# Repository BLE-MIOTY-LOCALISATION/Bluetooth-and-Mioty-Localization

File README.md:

This repository contains all the files related to research projects.

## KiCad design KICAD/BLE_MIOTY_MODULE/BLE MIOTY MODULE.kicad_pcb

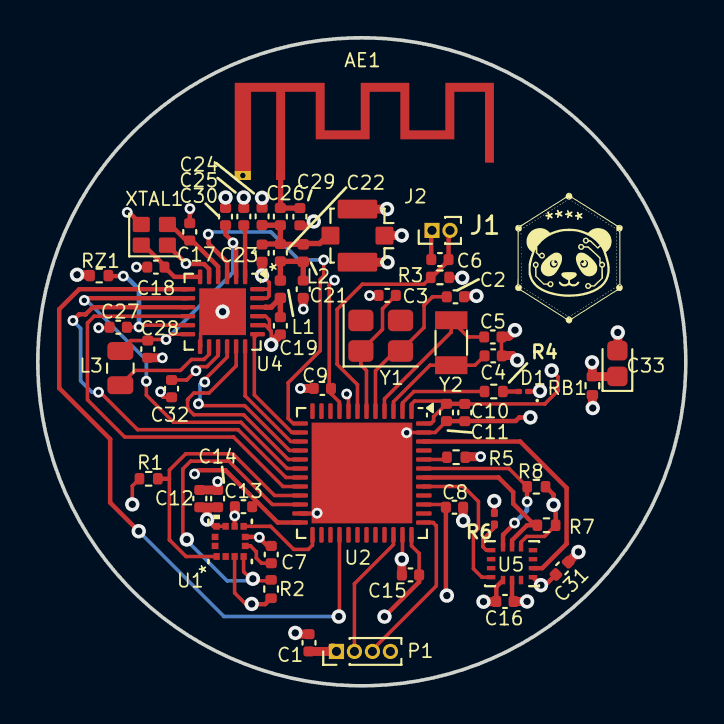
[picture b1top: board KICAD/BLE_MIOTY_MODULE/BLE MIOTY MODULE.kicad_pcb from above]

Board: 4 copper layers, 36.0 x 36.0 mm, 58 parts (1 on the bottom side), 41 nets.

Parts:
AE1: Antenna_Shield; Texas_SWRA117D_2.4GHz_Right
C1, C14: 0.1u; C_0402_1005Metric
C2, C3: 24p; C_0402_1005Metric
C4, C5: 14p; C_0402_1005Metric
C6: 1u; C_0402_1005Metric
C7: 220n; C_0402_1005Metric
C8, C9, C10, C11, C13, C15, C16, C27, C31, C32: 100n; C_0402_1005Metric
C12: 10u; C_0402_1005Metric
C17, C18: 10p; C_0402_1005Metric
C19: 0.8p; C_0402_1005Metric
C21, C23: 1.2p; C_0402_1005Metric
C22: 0.5p; C_0402_1005Metric
C24, C26, C29: 0; C_0402_1005Metric
C25, C30: 10n; C_0402_1005Metric
C28: 470n; C_0402_1005Metric
C33: CP_EIA-1608-08_AVX-J
D1: LED; LED_01005_0402Metric
J1: RST; PinHeader_1x02_P1.00mm_Vertical
J2: Conn_Coaxial; U.FL_Molex_MCRF_73412-0110_Vertical
L1: 3n; L_0402_1005Metric
L2: 2.5n; L_0402_1005Metric
L3: 15u; C_0805_2012Metric
P1: SWD; PinHeader_1x04_P1.00mm_Vertical
R1, R2, R7, R8: 4.7K; R_0402_1005Metric
R3: 10K; R_0402_1005Metric
R4: 2000R; R_0402_1005Metric
R5: 100K; R_0402_1005Metric
R6: 10k; R_0201_0603Metric
RB1: 20; R_0402_1005Metric
RZ1: R; R_0402_1005Metric
U1: IIS2MDCTR; LGA-12_2X2X0P7_STM
U2: STM32F103CBUx; QFN-48-1EP_7x7mm_P0.5mm_EP5.6x5.6mm
U3: CR2032; BatteryHolder_Keystone_3002_1x2032
U4: SX1280IMLTRT; QFN-24-1EP_4x4mm_P0.5mm_EP2.6x2.6mm
U5: ICM-45686; IC_ICM-45686
XTAL1: NX2016SA-52MHZ-EXS00A-CS06016; Crystal_SMD_SeikoEpson_FA128-4Pin_2.0x1.6mm
Y1: 8MHz; Crystal_SMD_3225-4Pin_3.2x2.5mm
Y2: 32.678KHz; Crystal_SMD_3215-2Pin_3.2x1.5mm

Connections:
ANA: C19.2, L1.1, U4.22 (RFIO)
BUSY: U2.28 (PB15), U4.7 (BUSY)
DIO1: U2.18 (PB0), U4.8 (DIO1)
DIO2: U2.19 (PB1), U4.9 (DIO2)
DIO3: U2.20 (PB2), U4.10 (DIO3)
GND: AE1.2 (Shield), C1.1, C2.1, C3.1, C4.1, C5.1, C6.2, C7.2, C8.2, C9.2, C10.2, C11.2, C12.2, C13.2, C14.2, C15.2, C16.2, C17.1, C18.2, C19.1, C21.1, C23.2, C24.2, C25.2, C27.2, C28.2, C29.2, C30.1, C31.2, C32.1, C33.2, D1.1 (K), J1.1, J2.2 (Ext), P1.4, R5.2, R6.2, U1.6 (GND), U1.8 (GND), U2.8 (VSSA), U2.23 (VSS), U2.35 (VSS), U2.47 (VSS), U2.49 (VSS), U3.2, U4.5 (GND), U4.13 (GND), U4.20 (GND), U4.21 (GND), U4.23 (GND), U4.24 (GND), U4.25 (EXP), U5.6 (GND), XTAL1.2, XTAL1.4
INT1A: U2.41 (PB5), U5.4 (INT1/INT)
INT1M: U1.7 (INT/DRDY), U2.25 (PB12)
INT2A: U2.46 (PB9), U5.9 (INT2/FSYNC/CLKIN)
LED: R4.2, U2.2 (PC13)
MISO: U2.16 (PA6), U4.16 (MISO_TX)
MOSI: U2.17 (PA7), U4.17 (MOSI_RX)
NRESET: C6.1, J1.2, R3.2, U2.7 (NRST)
NRST: U2.13 (PA3), U4.3 (~RESET)
NSS: U2.14 (PA4), U4.19 (~SS_CTS)
unnamed: AE1.1 (A), C26.1, C29.1
unnamed: C21.2, C22.2, L1.2, L2.1
unnamed: D1.2 (A), R4.1
unnamed: C22.1, C23.1, C24.1, C26.2, J2.1 (In), L2.2
unnamed: C7.1, U1.5 (C1)
unnamed: R5.1, U2.44 (BOOT0)
unnamed: C28.1, C30.2, L3.2, U4.2 (VDD_IN), U4.12 (DCC_FB)
unnamed: L3.1, U4.14 (DCC_SW)
unnamed: C27.1, RZ1.2, U4.11 (VBAT_IO)
unnamed: C25.1, U4.1 (VR_PA)
unnamed: C17.2, U4.4 (XTA), XTAL1.3
unnamed: C18.1, U4.6 (XTB), XTAL1.1
unnamed: R6.1, U5.1 (AP_SDO/AP_AD0)
OSCIN1: C2.2, U2.5 (PD0), Y1.2
OSCIN2: C4.2, U2.3 (PC14), Y2.2
OSCOUT1: C3.2, U2.6 (PD1), Y1.1
OSCOUT2: C5.2, U2.4 (PC15), Y2.1
SCK: U2.15 (PA5), U4.18 (SCK_~RTS)
SCL 1: R7.2, U2.42 (PB6), U5.13 (AP_SCL/AP_SCLK)
SCL 2: R1.2, U1.1 (SCL/SPC), U2.21 (PB10)
SDA 1: R8.1, U2.43 (PB7), U5.14 (AP_SDA/AP_SDIO/AP_SDI)
SDA 2: R2.2, U1.4 (SDA/SDI/SDO), U2.22 (PB11)
SwDCLK: P1.3, U2.37 (PA14)
SwDIO: P1.2, U2.34 (PA13)
VCC, 3.3V: C1.2, C8.1, C9.1, C10.1, C11.1, C12.1, C13.1, C14.1, C15.1, C16.1, C31.1, C32.2, C33.1, P1.1, R1.1, R2.1, R3.1, R7.1, R8.2, RB1.1, RZ1.1, U1.3 (CS), U1.9 (VDD), U1.10 (VDD_IO), U2.1 (VBAT), U2.9 (VDDA), U2.24 (VDD), U2.36 (VDD), U2.39 (PB3), U2.48 (VDD), U4.15 (VBAT), U5.5 (VDDIO), U5.8 (VDD), U5.12 (AP_CS)
VCC, 3.3V RAW: RB1.2, U3.1

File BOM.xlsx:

S. No. | Schematic No | Component | Details | Part number | URL | Price
Power Supply
1 | RB1 | Resistor | 20 | CRCW040220R0FKED | https://www.digikey.de/de/products/detail/vishay-dale/CRCW04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
2 | U3 | CR2032 | Battery | CR2032 | https://www.digikey.de/de/products/detail/jauch-quartz/CR203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
Reset Mechanism
1 | R3 | Resistor | 10K | CRCW040210K0FKED | https://www.digikey.de/en/products/detail/vishay-dale/CRCW04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
2 | C6 | Capacitor | 1u | C0402C105K8PACTU | https://www.digikey.de/en/products/detail/kemet/C0402C105K8P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
J Link
1 | C1 | Capacitor | 0.1u | CC0402KRX7R9BB104 | https://www.digikey.de/en/products/detail/yageo/CC0402KRX7R9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
Oscillator
1 | Y1 | Crtystal Osc | 8MHx | ECS-80-12-33-JGN-TR | https://www.digikey.de/en/products/detail/ecs-inc/ECS-80-12-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
2 | Y2 | Crtystal Osc | 32KHz | ABS07-32.768KHZ-7-T | https://www.digikey.de/en/products/detail/abracon-llc/abs07-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
3 | C2 | Capacitor | 24p | GRM1555C1H240GA01D | https://www.digikey.de/de/products/detail/murata-electronics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
4 | C3 | Capacitor | 24p | GRM1555C1H240GA01D | https://www.digikey.de/de/products/detail/murata-electronics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
5 | C4 | Capacitor | 14p | GJM1555C1H140GB01D | https://www.digikey.de/de/products/detail/murata-electronics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
6 | C5 | Capacitor | 14p | GJM1555C1H140GB01D | https://www.digikey.de/de/products/detail/murata-electronics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
LED
1 | R4 | Resistor | 2K | CRCW04022K00FKED | https://www.digikey.de/en/products/detail/vishay-dale/CRCW04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
2 | D1 | LED | Blue | XL-1005UBC | https://www.digikey.de/en/products/detail/xinglight/XL-1005U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
Microcontroller
1 | U2 | Microcontroller |  | STM32F103CBU6 | https://www.digikey.de/en/products/detail/stmicroelectronics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
2 | R5 | Resistor | 100K | CRCW0402100KFKED | https://www.digikey.de/en/products/detail/vishay-dale/CRCW04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
3 | C8 | Capacitor | 0.1u | CC0402KRX7R9BB104 | https://www.digikey.de/en/products/detail/yageo/CC0402KRX7R9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
4 | C9 | Capacitor | 0.1u | CC0402KRX7R9BB104 | https://www.digikey.de/en/products/detail/yageo/CC0402KRX7R9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
5 | C10 | Capacitor | 0.1u | CC0402KRX7R9BB104 | https://www.digikey.de/en/products/detail/yageo/CC0402KRX7R9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
6 | C11 | Capacitor | 0.1u | CC0402KRX7R9BB104 | https://www.digikey.de/en/products/detail/yageo/CC0402KRX7R9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
7 | C13 | Capacitor | 0.1u | CC0402KRX7R9BB104 | https://www.digikey.de/en/products/detail/yageo/CC0402KRX7R9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
8 | C15 | Capacitor | 0.1u | CC0402KRX7R9BB104 | https://www.digikey.de/en/products/detail/yageo/CC0402KRX7R9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
LoRa WAN Module
1 | XTAL1 | Crytal oscillator | 52M | CS06016-52M | https://www.digikey.de/de/products/detail/ndk-nihon-dempa-ko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
2 | C17 | Capacitor | 10p | GRM1555C1H100FA01D | https://www.digikey.de/de/products/detail/murata-electronics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
3 | C18 | Capacitor | 10p | GRM1555C1H100FA01D | https://www.digikey.de/de/products/detail/murata-electronics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
4 | L3 | Inductor | 15u | MLZ2012M150W | https://www.digikey.de/en/products/detail/tdk-corporation/ML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
5 | C25 | Capacitor | 10n | GRM155R71E103KA01D | https://www.digikey.de/en/products/detail/murata-electronics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
6 | C27 | Capacitor | 100n | GRM155R71C104KA88D | https://www.digikey.de/en/products/detail/murata-electronics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
7 | RZ1 | Resistor | 0n | CRCW04020000Z0ED | https://www.digikey.de/en/products/detail/vishay-dale/CRCW04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
8 | C32 | Capacitor | 100n | GRM155R71C104KA88D | https://www.digikey.de/en/products/detail/murata-electronics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
9 | C30 | Capacitor | 10n | GRM155R71E103KA01D | https://www.digikey.de/en/products/detail/murata-electronics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
10 | C28 | Capacitor | 470n | GRM155R61A474KE15D | https://www.digikey.de/en/products/detail/murata-electronics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
11 | U4 | Lora Wan |  | SX1280IMLTRT | https://www.digikey.de/en/products/detail/semtech-corporatio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
Antenna Frontend
1 | C19 | capacitor | 0.8p | GRM1555C1HR80BA01D | https://www.digikey.de/en/products/detail/murata-electronics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
2 | L1 | Inductor | 3n | LQW15AN3N0B80D | https://www.digikey.de/en/products/detail/murata-electronics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
3 | C21 | capacitor | 1.2p | GRM1555C1H1R2BA01D | https://www.digikey.de/en/products/detail/murata-electronics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
4 | C22 | capacitor | 0.5p | GRM1555C1HR50WA01D | https://www.digikey.de/en/products/detail/murata-electronics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
5 | L2 | Inductor | 2.5n | LQW15AN2N5C00D | https://www.digikey.de/en/products/detail/murata-electronics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
6 | C23 | capacitor | 1.2p | GRM1555C1H1R2BA01D | https://www.digikey.de/en/products/detail/murata-electronics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
7 | C26 | capacitor | 0
8 | J1 | Connector |  | CONMHF1-SMD-G-T | https://www.digikey.de/de/products/detail/te-connectivity-li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
9 | C24 | capacitor | 0
10 | C29 | capacitor | 0
Tantal Capacitor
1 | C33 | Tantal capacitor | 220u | T491D227K010AT | https://www.digikey.de/en/products/detail/kemet/T491D227K010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
Accelerometer
1 | U5 | Accelerometer | ICM-45686 | ICM-45686 | https://www.digikey.de/de/products/detail/tdk-invensense/ICM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
2 | R6 | Resistor | 10K | CRCW040210K0FKED | https://www.digikey.de/en/products/detail/vishay-dale/CRCW04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
3 | C16 | Capacitor | 0.1u | CC0402KRX7R9BB104 | https://www.digikey.de/en/products/detail/yageo/CC0402KRX7R9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
4 | R7 | Resistor | 4.7K | CRCW04024K70FKED | https://www.digikey.de/de/products/detail/vishay-dale/CRCW04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
5 | R8 | Resistor | 4.7K | CRCW04024K70FKED | https://www.digikey.de/de/products/detail/vishay-dale/CRCW04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
6 | C31 | Capacitor | 0.1u | CC0402KRX7R9BB104 | https://www.digikey.de/en/products/detail/yageo/CC0402KRX7R9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
Magnetometer
1 | U1 | Magnetometer | magnetoresistiv Sensor X, Y, Z Achse 12-LGA (2x2) | IIS2MDCTR | https://www.digikey.de/de/products/detail/stmicroelectronics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
2 | R1 | Resistor | 4.7K | CRCW04024K70FKED | https://www.digikey.de/de/products/detail/vishay-dale/CRCW04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
3 | R2 | Resistor | 4.7K | CRCW04024K70FKED | https://www.digikey.de/de/products/detail/vishay-dale/CRCW04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
4 | C7 | Capacitor | 220n | GRM155R71C224KA12D | https://www.digikey.de/de/products/detail/murata-electronics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
5 | C12 | Capacitor | 10u | GRM155R61A106ME11D | https://www.digikey.de/de/products/detail/murata-electronics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
6 | C14 | Capacitor | 0.1u | CC0402KRX7R9BB104 | https://www.digikey.de/en/products/detail/yageo/CC0402KRX7R9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

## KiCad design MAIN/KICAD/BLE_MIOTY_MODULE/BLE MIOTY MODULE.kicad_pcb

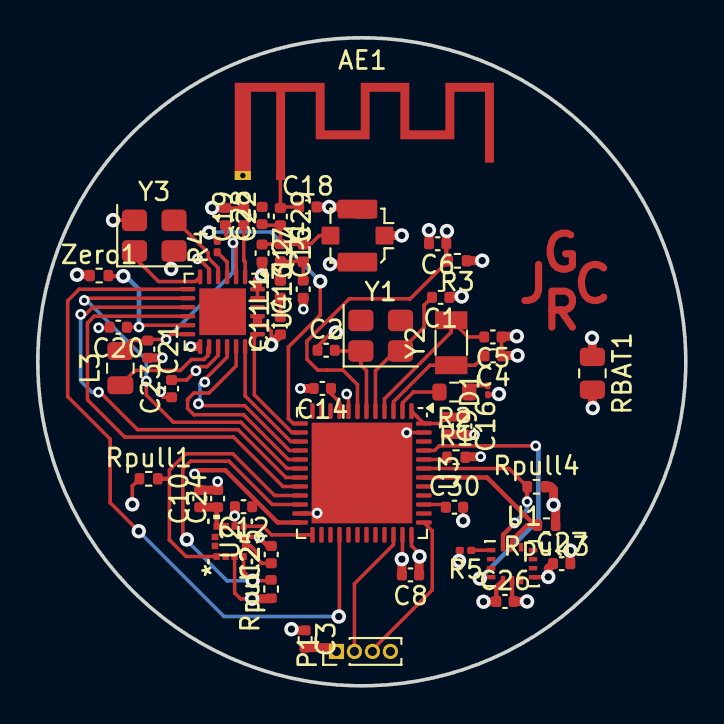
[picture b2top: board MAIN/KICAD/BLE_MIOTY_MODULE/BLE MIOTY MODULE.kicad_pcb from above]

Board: 4 copper layers, 36.0 x 36.0 mm, 55 parts (1 on the bottom side), 42 nets.

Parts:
AE1: Antenna_Shield; Texas_SWRA117D_2.4GHz_Right
C1, C2: 24p; C_0402_1005Metric
C3, C8, C9, C12, C14, C16, C24, C30: 0.1u; C_0402_1005Metric
C4, C5: 14p; C_0402_1005Metric
C6: 1u; C_0402_1005Metric
C10: 10u; C_0402_1005Metric
C11: 0.8p; C_0402_1005Metric
C13, C17: 1.2p; C_0402_1005Metric
C15: 0.5p; C_0402_1005Metric
C18, C28, C29: 0; C_0402_1005Metric
C19, C22: 10n; C_0402_1005Metric
C20, C23: 100n; C_0402_1005Metric
C21: 470n; C_0402_1005Metric
C25, C26, C27: 220n; C_0402_1005Metric
D1: LED; LED_01005_0402Metric
J1: Conn_Coaxial; U.FL_Molex_MCRF_73412-0110_Vertical
L1: 3n; L_0402_1005Metric
L2: 2.5n; L_0402_1005Metric
L3: 15u; C_0805_2012Metric
P1: SWD; PinHeader_1x04_P1.00mm_Vertical
R1: 100K; R_0402_1005Metric
R2: 2000R; R_0603_1608Metric
R3: 10K; R_0402_1005Metric
R4: R; R_0201_0603Metric
R5: 10k; R_0201_0603Metric
RBAT1: 20; R_0805_2012Metric
Rpull1, Rpull2, Rpull3, Rpull4: 4.7K; R_0402_1005Metric
U1: ICM-45686; IC_ICM-45686
U2: IIS2MDCTR; LGA-12_2X2X0P7_STM
U3: STM32F103CBUx; QFN-48-1EP_7x7mm_P0.5mm_EP5.6x5.6mm
U4: SX1280IMLTRT; QFN-24-1EP_4x4mm_P0.5mm_EP2.6x2.6mm
U5: CR2032; BatteryHolder_Keystone_3002_1x2032
Y1: 8MHz; Crystal_SMD_3225-4Pin_3.2x2.5mm
Y2: 32.678KHz; Crystal_SMD_3215-2Pin_3.2x1.5mm
Y3: 52M; Crystal_SMD_3225-4Pin_3.2x2.5mm
Zero1: R; R_0402_1005Metric

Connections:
ANA: C11.2, L1.1, U4.22 (RFIO)
BUSY: U3.28 (PB15), U4.7 (BUSY)
DIO1: U3.18 (PB0), U4.8 (DIO1)
DIO2: U3.19 (PB1), U4.9 (DIO2)
DIO3: U3.20 (PB2), U4.10 (DIO3)
GND: AE1.2 (Shield), C1.1, C2.1, C3.1, C4.1, C5.1, C6.2, C8.2, C9.2, C10.2, C11.1, C12.2, C13.1, C14.2, C16.2, C17.2, C18.2, C19.2, C20.2, C21.2, C22.1, C23.1, C24.2, C25.2, C26.2, C27.2, C28.2, C30.2, D1.1 (K), J1.2 (Ext), P1.4, R1.2, R5.2, U1.6 (GND), U2.6 (GND), U2.8 (GND), U3.8 (VSSA), U3.23 (VSS), U3.35 (VSS), U3.47 (VSS), U3.49 (VSS), U4.5 (GND), U4.13 (GND), U4.20 (GND), U4.21 (GND), U4.23 (GND), U4.24 (GND), U5.2, Y3.2, Y3.4
INT1: U1.4 (INT1/INT), U3.45 (PB8)
INT2: U2.7 (INT/DRDY), U3.25 (PB12)
LED: R2.2, U3.2 (PC13)
MISO: U3.16 (PA6), U4.16 (MISO_TX)
MOSI: U3.17 (PA7), U4.17 (MOSI_RX)
NRESET: C6.1, R3.2, U3.7 (NRST)
NRST: R4.2, U3.13 (PA3)
NSS: U3.14 (PA4), U4.19 (~SS_CTS)
unnamed: AE1.1 (A), C18.1, C29.1
unnamed: C13.2, C15.2, L1.2, L2.1
unnamed: D1.2 (A), R2.1
unnamed: C15.1, C17.1, C28.1, C29.2, J1.1 (In), L2.2
unnamed: R5.1, U1.1 (AP_SDO/AP_AD0)
unnamed: C25.1, U2.5 (C1)
unnamed: C10.1, C24.1, U2.9 (VDD), U2.10 (VDD_IO)
unnamed: R1.1, U3.44 (BOOT0)
unnamed: C21.1, C22.2, L3.2, U4.2 (VDD_IN), U4.12 (DCC_FB)
unnamed: L3.1, U4.14 (DCC_SW)
unnamed: C20.1, U4.11 (VBAT_IO), Zero1.2
unnamed: C19.1, U4.1 (VR_PA)
unnamed: U4.4 (XTA), Y3.3
unnamed: U4.6 (XTB), Y3.1
unnamed: R4.1, U4.3 (~RESET)
OSCIN1: C1.2, U3.5 (PD0), Y1.2
OSCIN2: C4.2, U3.3 (PC14), Y2.2
OSCOUT1: C2.2, U3.6 (PD1), Y1.1
OSCOUT2: C5.2, U3.4 (PC15), Y2.1
SCK: U3.15 (PA5), U4.18 (SCK_~RTS)
SCL 1: Rpull3.2, U1.13 (AP_SCL/AP_SCLK), U3.42 (PB6)
SCL 2: Rpull1.2, U2.1 (SCL/SPC), U3.21 (PB10)
SDA 1: Rpull4.1, U1.14 (AP_SDA/AP_SDIO/AP_SDI), U3.43 (PB7)
SDA 2: Rpull2.2, U2.4 (SDA/SDI/SDO), U3.22 (PB11)
SwDCLK: P1.3, U3.37 (PA14)
SwDIO: P1.2, U3.34 (PA13)
VCC, 3.3V: C3.2, C8.1, C9.1, C12.1, C14.1, C16.1, C23.2, C26.1, C27.1, C30.1, P1.1, R3.1, RBAT1.1, Rpull1.1, Rpull2.1, Rpull3.1, Rpull4.2, U1.5 (VDDIO), U1.8 (VDD), U2.3 (CS), U3.1 (VBAT), U3.9 (VDDA), U3.24 (VDD), U3.36 (VDD), U3.39 (PB3), U3.48 (VDD), U4.15 (VBAT), Zero1.1
VCC, 3.3V RAW: RBAT1.2, U5.1

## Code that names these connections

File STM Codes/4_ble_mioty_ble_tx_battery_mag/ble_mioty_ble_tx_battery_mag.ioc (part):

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Mcu.Name=STM32F103CBUx
Mcu.Package=UFQFPN48
Mcu.UserName=STM32F103CBUx
PA13.Mode=Serial_Wire
PA13.Signal=SYS_JTMS-SWDIO
PA14.Mode=Serial_Wire
PA14.Signal=SYS_JTCK-SWCLK
PA4.GPIOParameters=GPIO_Label
PA4.GPIO_Label=LORA_NSS
PA4.Signal=GPIO_Output
PA5.Mode=Full_Duplex_Master
PA5.Signal=SPI1_SCK
PA6.Mode=Full_Duplex_Master
PA6.Signal=SPI1_MISO
PA7.Mode=Full_Duplex_Master
PA7.Signal=SPI1_MOSI
PB0.GPIOParameters=GPIO_Label
PB0.GPIO_Label=LORA_DIO1
PB0.Signal=GPIO_Input
PB10.Mode=I2C
PB10.Signal=I2C2_SCL
PB11.Mode=I2C
PB11.Signal=I2C2_SDA
PB12.GPIOParameters=GPIO_Label
PB12.GPIO_Label=MAG INT
PB12.Signal=GPXTI12
PB15.GPIOParameters=GPIO_Label
PB15.GPIO_Label=LORA_BUSY
PB15.Signal=GPIO_Input
PC13-TAMPER-RTC.GPIOParameters=GPIO_Label
PC13-TAMPER-RTC.GPIO_Label=LED
PC13-TAMPER-RTC.Signal=GPIO_Output
PC14-OSC32_IN.Mode=LSE-External-Oscillator
PC14-OSC32_IN.Signal=RCC_OSC32_IN
PC15-OSC32_OUT.Mode=LSE-External-Oscillator
PC15-OSC32_OUT.Signal=RCC_OSC32_OUT
PD0-OSC_IN.Mode=HSE-External-Oscillator
PD0-OSC_IN.Signal=RCC_OSC_IN
PD1-OSC_OUT.Mode=HSE-External-Oscillator
PD1-OSC_OUT.Signal=RCC_OSC_OUT
RCC.SYSCLKFreq_VALUE=8000000
RCC.SYSCLKSource=RCC_SYSCLKSOURCE_HSE
board=custom

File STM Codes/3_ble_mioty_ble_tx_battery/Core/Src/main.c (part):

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  uint8_t crc_seed[3] = {0x55, 0x55, 0x55};
  SX1280_WriteRegister(0x09C7, crc_seed, 3);

  // 8. Map TxDone IRQ to DIO1 pin
  //    [opcode, IRQmask_H, IRQmask_L, DIO1_H, DIO1_L, DIO2_H, DIO2_L, DIO3_H,
  //    DIO3_L]
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// -----------------------------------------------------------------------
// Transmit one BLE ADV_NONCONN_IND packet on the specified channel
//
// Returns: 1 = TxDone confirmed via DIO1 pin
//          0 = TxDone not seen (possible TX failure)
//
// DIO1 is mapped to TxDone IRQ in InitBLE step 8.
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  SX1280_WaitBusy();
  HAL_Delay(2);

  // Read TxDone confirmation from DIO1 pin
  uint8_t txdone = 0;
  if (HAL_GPIO_ReadPin(LORA_DIO1_GPIO_Port, LORA_DIO1_Pin) == GPIO_PIN_SET) {
    txdone = 1;
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  __HAL_SPI_DISABLE(&hspi1);

  GPIO_InitTypeDef GPIO_InitStruct = {0};
  // SCK (PA5), MISO (PA6), MOSI (PA7) -> Input with Pull-Down (prevents floating SPI bus)
  GPIO_InitStruct.Pin = GPIO_PIN_5 | GPIO_PIN_6 | GPIO_PIN_7;
  GPIO_InitStruct.Mode = GPIO_MODE_INPUT;
  GPIO_InitStruct.Pull = GPIO_PULLDOWN;
  HAL_GPIO_Init(GPIOA, &GPIO_InitStruct);

  // DIO1 (PB0) and BUSY (PB15) -> Input with Pull-Down
  GPIO_InitStruct.Pin = LORA_DIO1_Pin | LORA_BUSY_Pin;
  GPIO_InitStruct.Mode = GPIO_MODE_INPUT;
  GPIO_InitStruct.Pull = GPIO_PULLDOWN;
  HAL_GPIO_Init(GPIOB, &GPIO_InitStruct);

  // Keep NSS (PA4) and NRST (PA3) HIGH to lock radio state
  HAL_GPIO_WritePin(LORA_NSS_GPIO_Port, LORA_NSS_Pin, GPIO_PIN_SET);
  HAL_GPIO_WritePin(LORA_NRST_GPIO_Port, LORA_NRST_Pin, GPIO_PIN_SET);

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  HAL_SPI_DeInit(&hspi1);
  MX_SPI1_Init();

  // 9. Re-initialize DIO1 (PB0) and BUSY (PB15) as INPUT, NOPULL
  GPIO_InitStruct.Pin = LORA_DIO1_Pin | LORA_BUSY_Pin;
  GPIO_InitStruct.Mode = GPIO_MODE_INPUT;
  GPIO_InitStruct.Pull = GPIO_NOPULL;
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
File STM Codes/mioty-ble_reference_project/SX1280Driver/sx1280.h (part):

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#include <cmath>

/*!
 * \brief GPIO pin number connected to DIO1 on the SX1280 radio module.
 *
 * DIO1 is used by the SX1280 to signal events like payload ready, transmission done, etc.
 * This pin must be configured as an input and, depending on the specific use case,
 * may need to trigger interrupts.
 */
#define PIN_DIO1 2

/*!
 * \brief GPIO pin number connected to DIO2 on the SX1280 radio module.
 *
 * DIO2 is typically used for signaling events such as FHSS frequency change, CAD detection, etc.
 * Similar to DIO1, this pin should be configured based on the intended radio functionalities being used.
 */
#define PIN_DIO2 3

/*!
 * \brief GPIO pin number connected to DIO3 on the SX1280 radio module.
 *
 * DIO3 can be used for additional event signaling from the SX1280, which may include timing or synchronization signals.
 * Configuration and use will depend on the SX1280's operational mode and setup.
 */
#define PIN_DIO3 4

/*!
 * \brief Provides the frequency of the chip running on the radio and the frequency step
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
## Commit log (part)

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2025-07-01 Previous Project Injection
2025-07-01 Progress 1
2025-08-13 Added a new folder and datsheets
2025-08-15 updated kicad design and bluepill schematic files
2025-08-15 Added CR2032, start with PCB schematic
2025-08-15 Did something
2025-08-18 Updated Repo Structure, updated schematic v1.1
2025-08-20 Updated PCB Design
2025-09-03 latest with lad9s1 acc and tantal
2025-09-03 Updated latest with all files
2025-09-11 Updated components acording to BOM
2025-10-14 New Beginings
2025-10-14 Organization
2025-10-14 Some more
2025-10-16 updated Link in BOM
2025-10-16 Deleting V2
2025-10-16 Added 5 Caps, Excel changes
2025-10-16 Y3 Tental Pending, Start PCB, BOM Updated
2025-10-17 latest push
2025-10-17 PCB Premier League
2025-10-17 RCBavaria First Push
2025-10-23 Fresh PCB start
2025-10-23 RC: Added Footprints Folder, Added New IMUs Sym/ Footprint
2025-10-23 Sync
2025-10-23 STM ref
2025-10-23 first proto
2025-10-27 new design on main
2025-10-27 minor change
2025-10-31 sync 2
2025-10-31 Sync 3
2025-11-05 final push
    updated BOM and PCB
2025-12-03 Latest changes with 0 errors effective
2025-12-03 change of track width required
2025-12-04 Final Design for Production
2025-12-11 sync with BOM
2026-05-21 blink code with blue pill working
2026-05-21 pin update
2026-05-27 Clean Up
2026-05-29 Folder Management
2026-06-05 LORA Bring Up Done
2026-06-05 Lora TX code, updated Schematic (fix duplicate annotations), exported netlist
2026-06-05 Added BLE TX STM Code
2026-06-07 9-6-3 latest
2026-06-10 Transmitter Woring, BLE N/A
2026-06-10 Few Changes
2026-06-11 BLE Working
2026-06-11 Updated Schematic, BOM, Add Symbols and completed 3d view
2026-06-11 Update BOM, remove lock file
2026-06-11 changed tantal ref C33
2026-06-11 Updated PCB, Schematic, 3D Model
2026-06-11 removed lc files
2026-06-24 Remove old PlatformIO files and add GoogleFindMyTools and MIOTY_BLE_Tests which includes optimized Ble_tx_codes
2026-06-25 feat(power-opt): fix compilation, enable LSE/Low-power loop, and correct LED polarity
    - Fix compilation by declaring volatile 'alarm_fired' flag.
    - Populate empty main loop with BLE beacon transmission and Stop Mode entry.
    - Configure LORA_NRST (PA3) as GPIO output to prevent floating radio reset states.
    - Correct LED pin mapping for active-high polarity to eliminate sleep current leakage.
    - Switch RTC clock source to LSE (32.768 kHz) with a 32767 prescaler for accurate 1 Hz wakeup.
    - Add RSF flag synchronization to RTC_SetAlarm_1s() to prevent corrupted register reads after Stop Mode wakeup.
2026-06-25 Added How_The_Code_Works.md file
2026-06-28 Add battery BLE projects and documentation
